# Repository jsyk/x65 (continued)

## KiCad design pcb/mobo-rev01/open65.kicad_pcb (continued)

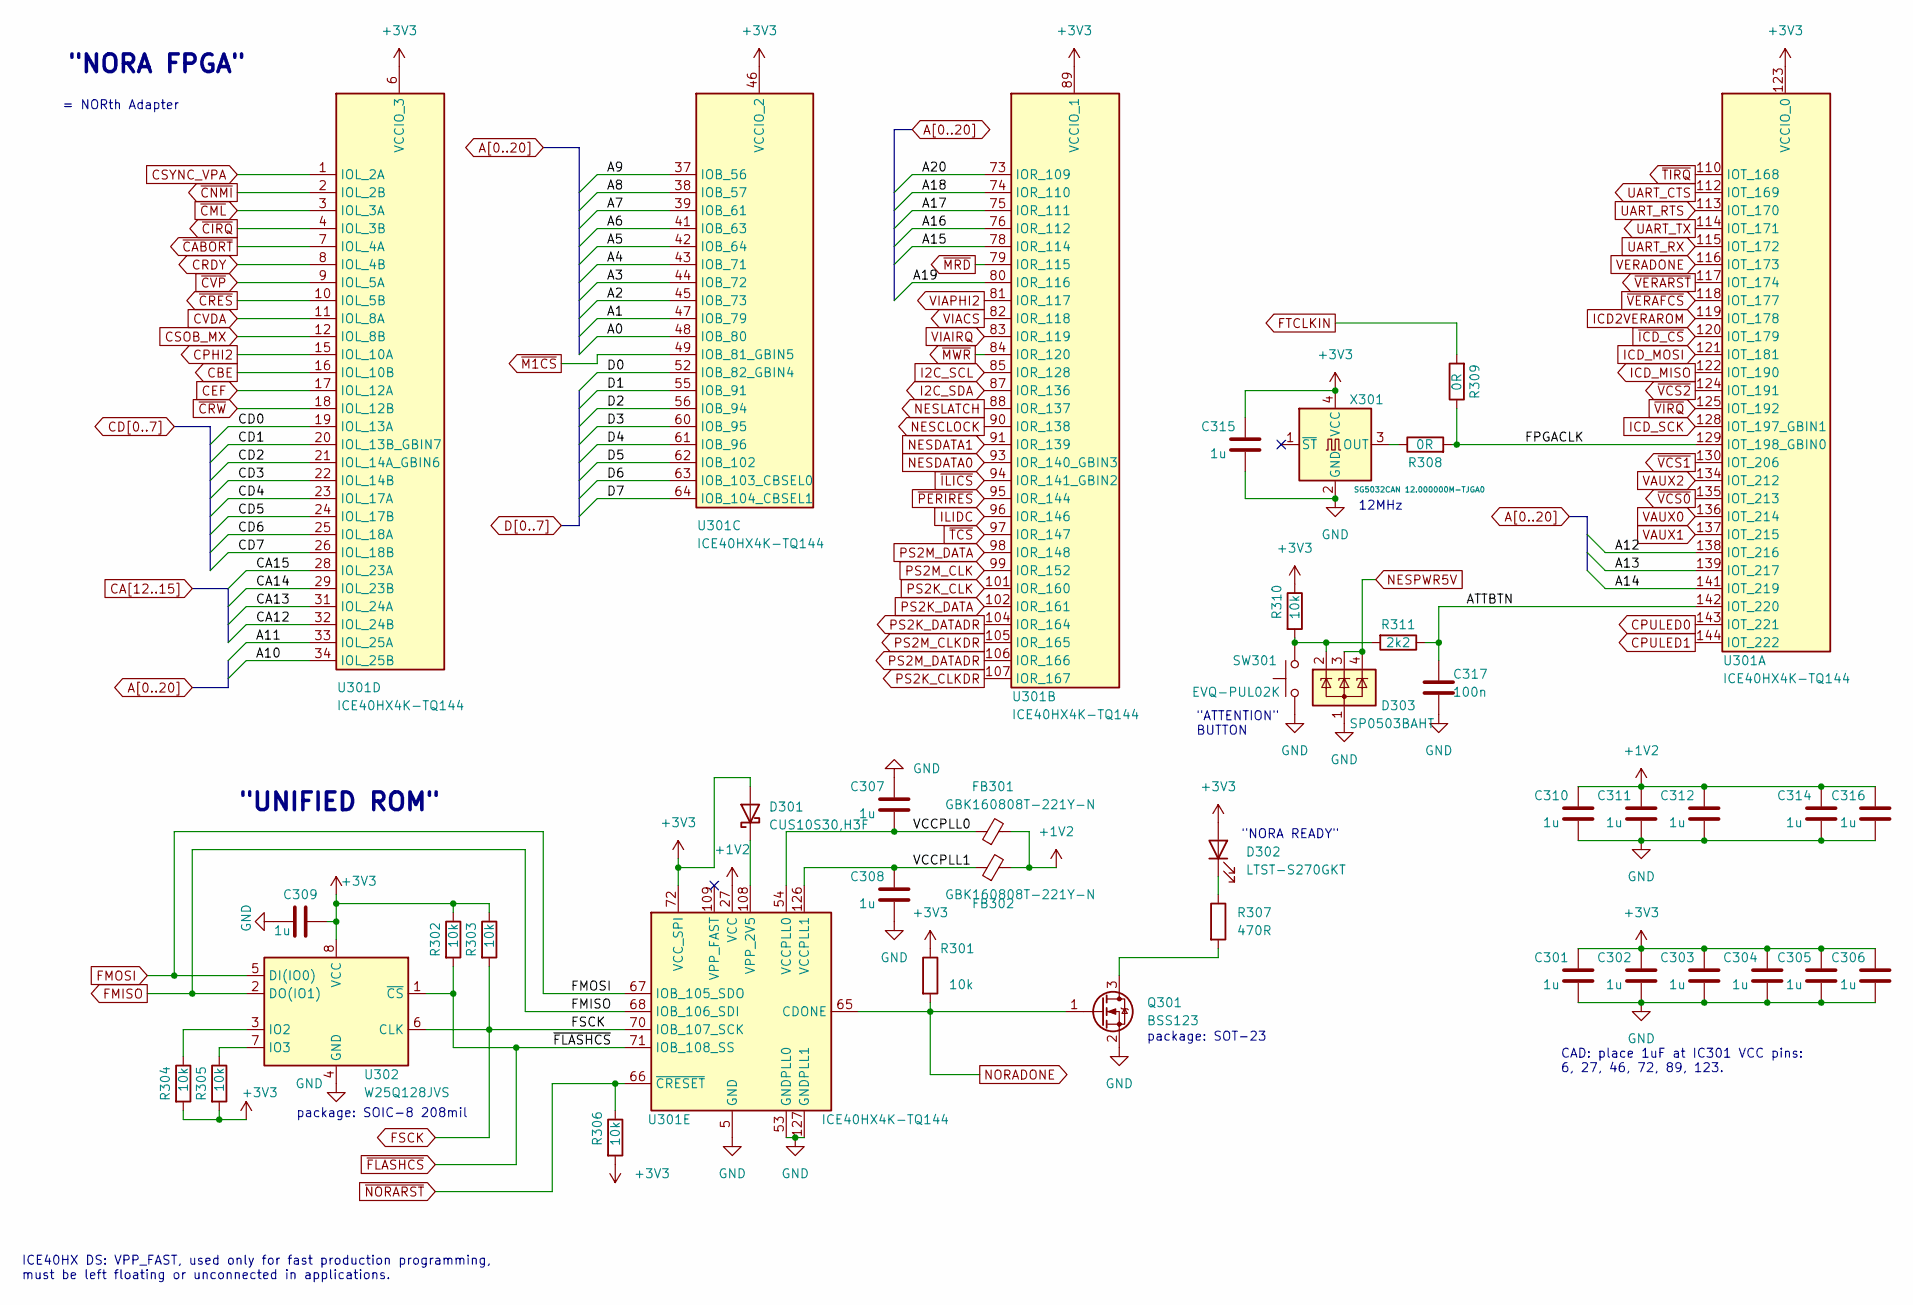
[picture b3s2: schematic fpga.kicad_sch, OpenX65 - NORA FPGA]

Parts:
C301, C302, C303, C304, C305, C306, C307, C308, C309, C310, C311, C312, C314, C315, C316: 1u; C_0603_1608Metric_Pad1.08x0.95mm_HandSolder
C317: 100n; C_0603_1608Metric_Pad1.08x0.95mm_HandSolder
D301: CUS10S30,H3F; D_SOD-323_HandSoldering
D302: LTST-S270GKT; LED_0603_1608Metric_Pad1.05x0.95mm_HandSolder
D303: SP0503BAHT; SOT-143
FB301, FB302: GBK160808T-221Y-N; R_0603_1608Metric_Pad0.98x0.95mm_HandSolder
Q301: BSS123; SOT-23
R301, R302, R303, R304, R305, R306, R310: 10k; R_0603_1608Metric_Pad0.98x0.95mm_HandSolder
R307: 470R; R_0603_1608Metric_Pad0.98x0.95mm_HandSolder
R308, R309: 0R; R_0603_1608Metric_Pad0.98x0.95mm_HandSolder
R311: 2k2; R_0603_1608Metric_Pad0.98x0.95mm_HandSolder
SW301: EVQ-PUL02K; Panasonic_EVQPUL_EVQPUC
U301: ICE40HX4K-TQ144; TQFP-144_20x20mm_P0.5mm
U302: W25Q128JVS; SOIC-8_5.23x5.23mm_P1.27mm
X301: SG5032CAN 12.000000M-TJGA0; Oscillator_SMD_SeikoEpson_SG8002LB-4Pin_5.0x3.2mm_HandSolde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

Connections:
+1V2: C310.1, C311.1, C312.1, C314.1, C316.1, FB301.2, FB302.2, U301.27 (VCC), U301.40 (VCC), U301.92 (VCC), U301.111 (VCC); also elsewhere on the board
+3V3: C301.1, C302.1, C303.1, C304.1, C305.1, C306.1, C309.1, C315.1, D301.2 (A), D302.2 (A), R301.1, R302.1, R303.1, R304.2, R305.2, R306.2, R310.1, U301.6 (VCCIO_3), U301.30 (VCCIO_3), U301.46 (VCCIO_2), U301.57 (VCCIO_2), U301.72 (VCC_SPI), U301.89 (VCCIO_1), U301.100 (VCCIO_1), U301.123 (VCCIO_0), U301.131 (VCCIO_0), U302.8 (VCC), X301.4 (VCC); also elsewhere on the board
/FPGA/ATTBTN: C317.1, R311.1, U301.142 (IOT_220)
/FPGA/FPGACLK: R308.2, R309.1, U301.129 (IOT_198_GBIN0)
/FPGA/VCCPLL0: C307.2, FB301.1, U301.54 (VCCPLL0)
/FPGA/VCCPLL1: C308.1, FB302.1, U301.126 (VCCPLL1)
A0: U301.48 (IOB_80); also elsewhere on the board
A1: U301.47 (IOB_79); also elsewhere on the board
A2: U301.45 (IOB_73); also elsewhere on the board
A3: U301.44 (IOB_72); also elsewhere on the board
A4: U301.43 (IOB_71); also elsewhere on the board
A5: U301.42 (IOB_64); also elsewhere on the board
A6: U301.41 (IOB_63); also elsewhere on the board
A7: U301.39 (IOB_61); also elsewhere on the board
A8: U301.38 (IOB_57); also elsewhere on the board
A9: U301.37 (IOB_56); also elsewhere on the board
A10: U301.34 (IOL_25B); also elsewhere on the board
A11: U301.33 (IOL_25A); also elsewhere on the board
A12: U301.138 (IOT_216); also elsewhere on the board
A13: U301.139 (IOT_217); also elsewhere on the board
A14: U301.141 (IOT_219); also elsewhere on the board
A15: U301.78 (IOR_114); also elsewhere on the board
A16: U301.76 (IOR_112); also elsewhere on the board
A17: U301.75 (IOR_111); also elsewhere on the board
A18: U301.74 (IOR_110); also elsewhere on the board
A19: U301.80 (IOR_116); also elsewhere on the board
A20: U301.73 (IOR_109); also elsewhere on the board
CA12: U301.32 (IOL_24B); also elsewhere on the board
CA13: U301.31 (IOL_24A); also elsewhere on the board
CA14: U301.29 (IOL_23B); also elsewhere on the board
CA15: U301.28 (IOL_23A); also elsewhere on the board
CBE: U301.16 (IOL_10B); also elsewhere on the board
CD0: U301.19 (IOL_13A); also elsewhere on the board
CD1: U301.20 (IOL_13B_GBIN7); also elsewhere on the board
CD2: U301.21 (IOL_14A_GBIN6); also elsewhere on the board
CD3: U301.22 (IOL_14B); also elsewhere on the board
CD4: U301.23 (IOL_17A); also elsewhere on the board
CD5: U301.24 (IOL_17B); also elsewhere on the board
CD6: U301.25 (IOL_18A); also elsewhere on the board
CD7: U301.26 (IOL_18B); also elsewhere on the board
CEF: U301.17 (IOL_12A); also elsewhere on the board
CPHI2: U301.15 (IOL_10A); also elsewhere on the board
CPULED0: U301.143 (IOT_221); also elsewhere on the board
CPULED1: U301.144 (IOT_222); also elsewhere on the board
CRDY: U301.8 (IOL_4B); also elsewhere on the board
CSOB_MX: U301.12 (IOL_8B); also elsewhere on the board
CSYNC_VPA: U301.1 (IOL_2A); also elsewhere on the board
CVDA: U301.11 (IOL_8A); also elsewhere on the board
D0: U301.52 (IOB_82_GBIN4); also elsewhere on the board
D1: U301.55 (IOB_91); also elsewhere on the board
D2: U301.56 (IOB_94); also elsewhere on the board
D3: U301.60 (IOB_95); also elsewhere on the board
D4: U301.61 (IOB_96); also elsewhere on the board
D5: U301.62 (IOB_102); also elsewhere on the board
D6: U301.63 (IOB_103_CBSEL0); also elsewhere on the board
D7: U301.64 (IOB_104_CBSEL1); also elsewhere on the board
FMISO: U301.68 (IOB_106_SDI), U302.2 (DO(IO1)); also elsewhere on the board
FMOSI: U301.67 (IOB_105_SDO), U302.5 (DI(IO0)); also elsewhere on the board
FSCK: R303.2, U301.70 (IOB_107_SCK), U302.6 (CLK); also elsewhere on the board
FTCLKIN: R309.2; also elsewhere on the board
GND: C301.2, C302.2, C303.2, C304.2, C305.2, C306.2, C307.1, C308.2, C309.2, C310.2, C311.2, C312.2, C314.2, C315.2, C316.2, C317.2, D303.1 (A), Q301.2 (S), SW301.1, U301.5 (GND), U301.13 (GND), U301.14 (GND), U301.53 (GNDPLL0), U301.59 (GND), U301.69 (GND), U301.86 (GND), U301.103 (GND), U301.127 (GNDPLL1), U301.132 (GND), U301.140 (GND), U302.4 (GND), X301.2 (GND); also elsewhere on the board
I2C_SCL: U301.85 (IOR_128); also elsewhere on the board
I2C_SDA: U301.87 (IOR_136); also elsewhere on the board
ICD2VERAROM: U301.119 (IOT_178); also elsewhere on the board
ICD_MISO: U301.122 (IOT_190); also elsewhere on the board
ICD_MOSI: U301.121 (IOT_181); also elsewhere on the board
ICD_SCK: U301.128 (IOT_197_GBIN1); also elsewhere on the board
ILIDC: U301.96 (IOR_146); also elsewhere on the board
NESCLOCK: U301.90 (IOR_138); also elsewhere on the board
NESDATA0: U301.93 (IOR_140_GBIN3); also elsewhere on the board
NESDATA1: U301.91 (IOR_139); also elsewhere on the board
NESLATCH: U301.88 (IOR_137); also elsewhere on the board
NESPWR5V: D303.3 (K), D303.4 (K); also elsewhere on the board
NORADONE: Q301.1 (G), R301.2, U301.65 (CDONE); also elsewhere on the board
unnamed: D301.1 (K), U301.108 (VPP_2V5)
unnamed: D302.1 (K), R307.1
unnamed: D303.2 (K), R310.2, R311.2, SW301.2
unnamed: Q301.3 (D), R307.2
unnamed: R304.1, U302.3 (IO2)
unnamed: R305.1, U302.7 (IO3)
unnamed: R308.1, X301.3 (OUT)
PS2K_CLK: U301.101 (IOR_160); also elsewhere on the board
PS2K_CLKDR: U301.107 (IOR_167); also elsewhere on the board
PS2K_DATA: U301.102 (IOR_161); also elsewhere on the board
PS2K_DATADR: U301.104 (IOR_164); also elsewhere on the board
PS2M_CLK: U301.99 (IOR_152); also elsewhere on the board
PS2M_CLKDR: U301.105 (IOR_165); also elsewhere on the board
PS2M_DATA: U301.98 (IOR_148); also elsewhere on the board
PS2M_DATADR: U301.106 (IOR_166); also elsewhere on the board
UART_CTS: U301.112 (IOT_169); also elsewhere on the board
UART_RTS: U301.113 (IOT_170); also elsewhere on the board
UART_RX: U301.115 (IOT_172); also elsewhere on the board
UART_TX: U301.114 (IOT_171); also elsewhere on the board
VAUX0: U301.136 (IOT_214); also elsewhere on the board
VAUX1: U301.137 (IOT_215); also elsewhere on the board
VAUX2: U301.134 (IOT_212); also elsewhere on the board
VERADONE: U301.116 (IOT_173); also elsewhere on the board
VIACS: U301.82 (IOR_118); also elsewhere on the board
VIAIRQ: U301.83 (IOR_119); also elsewhere on the board
VIAPHI2: U301.81 (IOR_117); also elsewhere on the board
~CABORT: U301.7 (IOL_4A); also elsewhere on the board
~CIRQ: U301.4 (IOL_3B); also elsewhere on the board
~CML: U301.3 (IOL_3A); also elsewhere on the board
~CNMI: U301.2 (IOL_2B); also elsewhere on the board
~CRES: U301.10 (IOL_5B); also elsewhere on the board
~CRW: U301.18 (IOL_12B); also elsewhere on the board
~CVP: U301.9 (IOL_5A); also elsewhere on the board
~FLASHCS: R302.2, U301.71 (IOB_108_SS), U302.1 (~CS); also elsewhere on the board
~ICD_CS: U301.120 (IOT_179); also elsewhere on the board
~ILICS: U301.94 (IOR_141_GBIN2); also elsewhere on the board
~M1CS: U301.49 (IOB_81_GBIN5); also elsewhere on the board
~MRD: U301.79 (IOR_115); also elsewhere on the board
~MWR: U301.84 (IOR_120); also elsewhere on the board
~NORARST: R306.1, U301.66 (~CRESET); also elsewhere on the board
~PERIRES: U301.95 (IOR_144); also elsewhere on the board
~TCS: U301.97 (IOR_147); also elsewhere on the board
~TIRQ: U301.110 (IOT_168); also elsewhere on the board
~VCS0: U301.135 (IOT_213); also elsewhere on the board
~VCS1: U301.130 (IOT_206); also elsewhere on the board
~VCS2: U301.124 (IOT_191); also elsewhere on the board
~VERAFCS: U301.118 (IOT_177); also elsewhere on the board
~VERARST: U301.117 (IOT_174); also elsewhere on the board
~VIRQ: U301.125 (IOT_192); also elsewhere on the board

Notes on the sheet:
package: SOIC-8 208mil
12MHz
= NORth Adapter
ICE40HX DS: VPP_FAST, used only for fast production programming, must be left floating or unconnected in applications.
"NORA READY"
"NORA FPGA"
"UNIFIED ROM"
package: SOT-23
"ATTENTION" BUTTON
CAD: place 1uF at IC301 VCC pins: 6, 27, 46, 72, 89, 123.

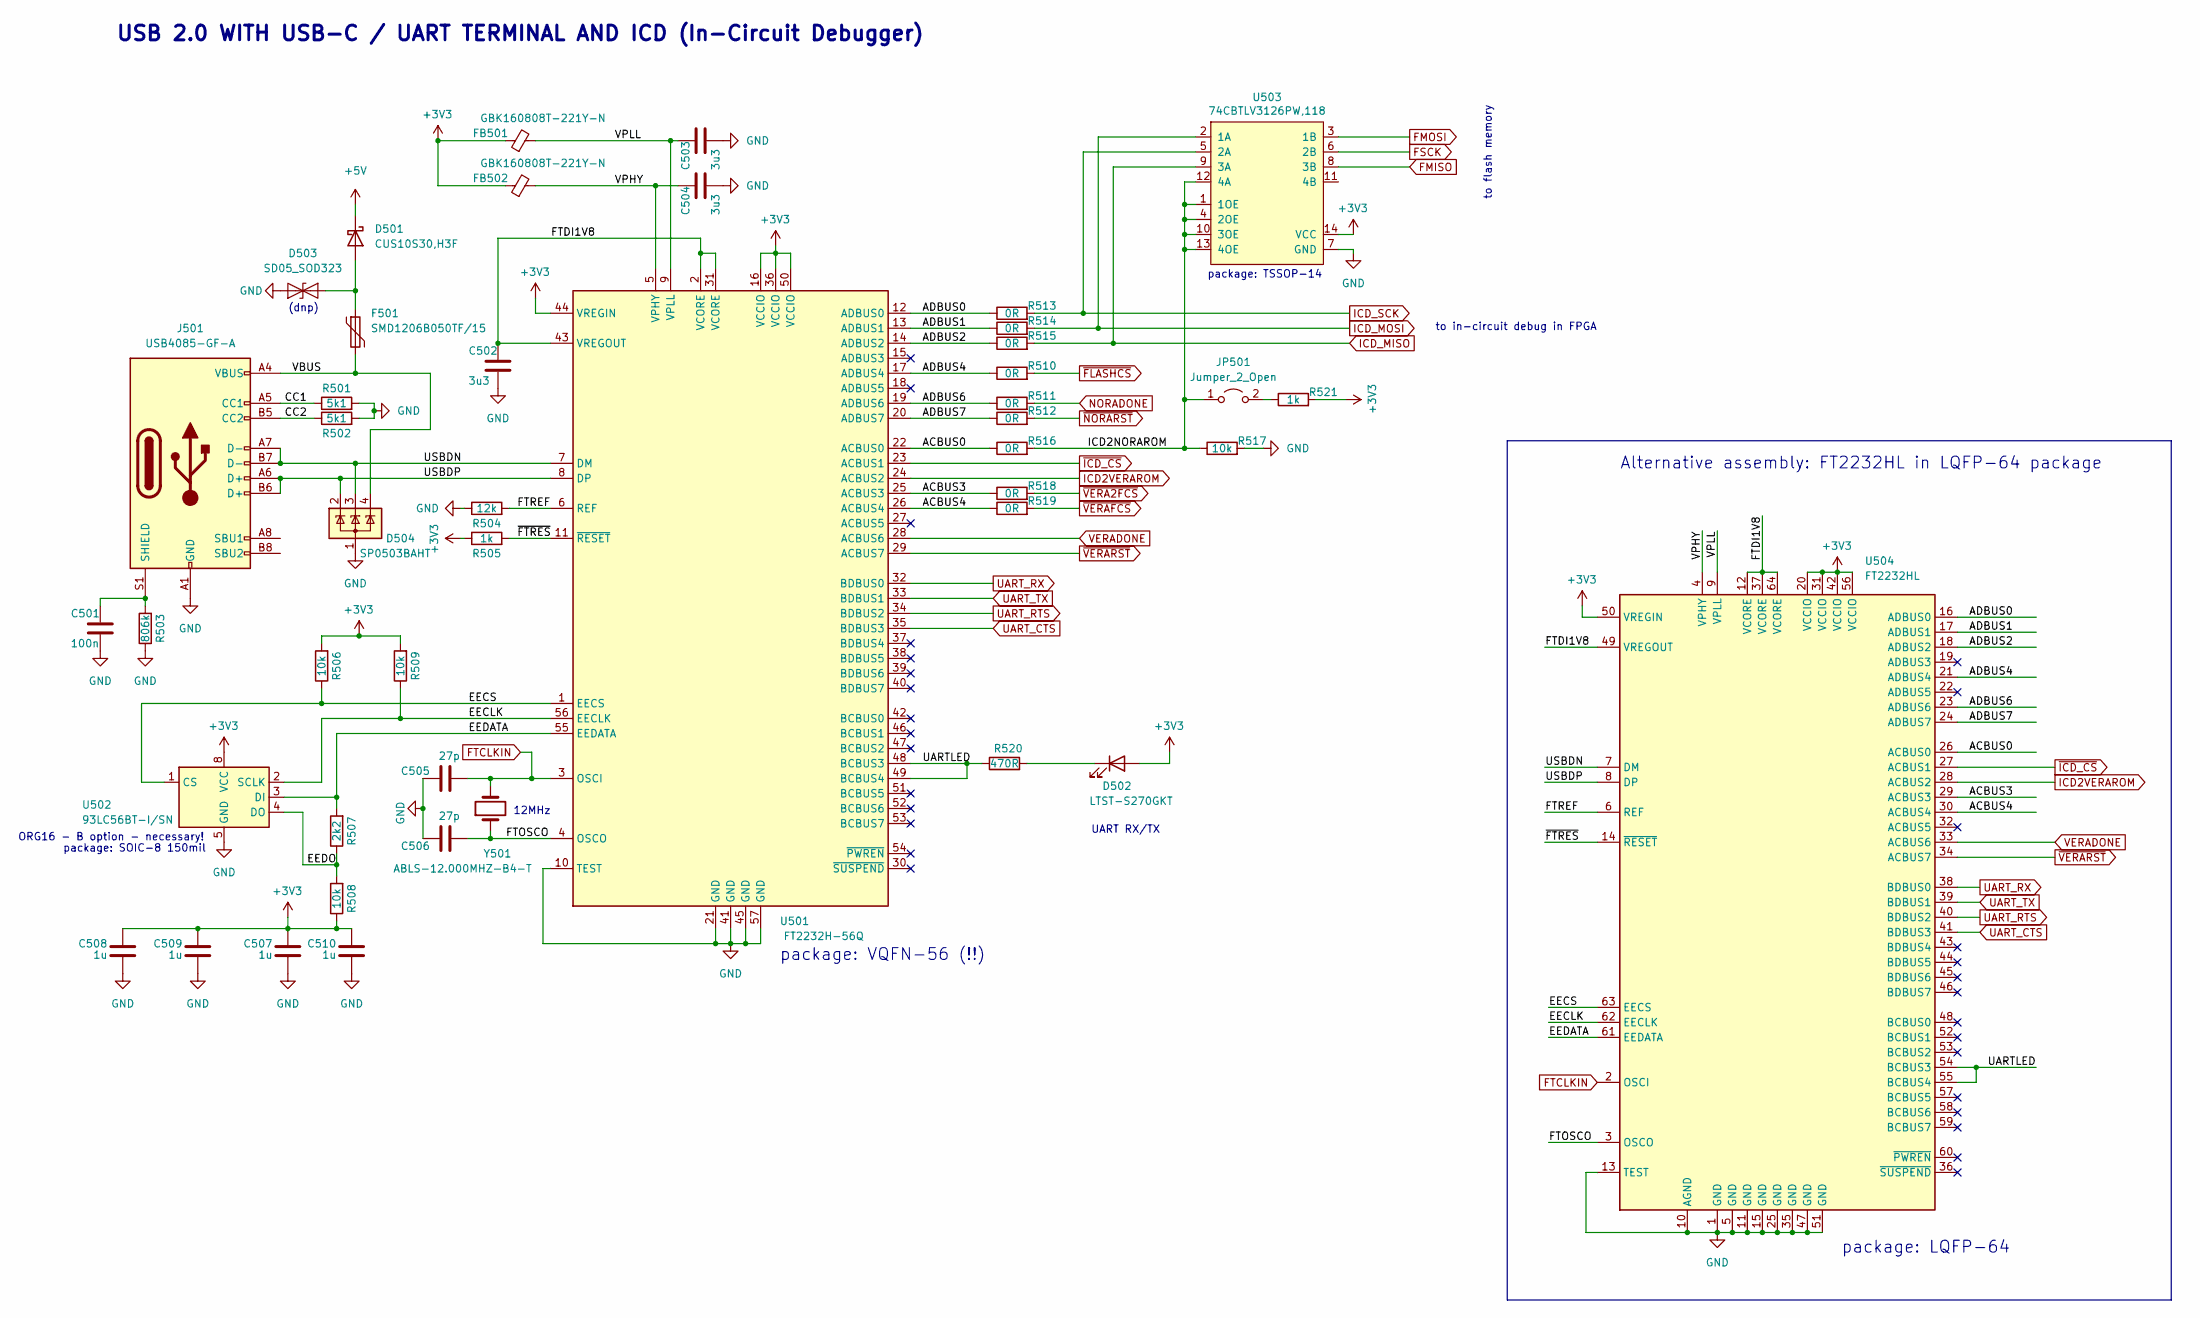
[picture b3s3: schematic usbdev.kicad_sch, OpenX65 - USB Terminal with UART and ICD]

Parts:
C501: 100n; C_0603_1608Metric_Pad1.08x0.95mm_HandSolder
C502, C503, C504: 3u3; C_0603_1608Metric_Pad1.08x0.95mm_HandSolder
C505, C506: 27p; C_0603_1608Metric_Pad1.08x0.95mm_HandSolder
C507, C508, C509, C510: 1u; C_0603_1608Metric_Pad1.08x0.95mm_HandSolder
D501: CUS10S30,H3F; D_SOD-323_HandSoldering
D502: LTST-S270GKT; LED_0603_1608Metric_Pad1.05x0.95mm_HandSolder
D503: SD05_SOD323; D_SOD-323
D504: SP0503BAHT; SOT-143
F501: SMD1206B050TF/15; Fuse_1206_3216Metric_Pad1.42x1.75mm_HandSolder
FB501, FB502: GBK160808T-221Y-N; R_0603_1608Metric_Pad0.98x0.95mm_HandSolder
J501: USB4085-GF-A; USB_C_Receptacle_GCT_USB4085
JP501: Jumper_2_Open; PinHeader_1x02_P2.54mm_Vertical
R501, R502: 5k1; R_0603_1608Metric_Pad0.98x0.95mm_HandSolder
R503: 806k; R_0603_1608Metric_Pad0.98x0.95mm_HandSolder
R504: 12k; R_0603_1608Metric_Pad0.98x0.95mm_HandSolder
R505, R521: 1k; R_0603_1608Metric_Pad0.98x0.95mm_HandSolder
R506, R508, R509, R517: 10k; R_0603_1608Metric_Pad0.98x0.95mm_HandSolder
R507: 2k2; R_0603_1608Metric_Pad0.98x0.95mm_HandSolder
R510, R511, R512, R513, R514, R515, R516, R518, R519: 0R; R_0603_1608Metric_Pad0.98x0.95mm_HandSolder
R520: 470R; R_0603_1608Metric_Pad0.98x0.95mm_HandSolder
U501: FT2232H-56Q; QFN-56-1EP_8x8mm_P0.5mm_EP4.5x5.2mm
U502: 93LC56BT-I/SN; SOIC-8_3.9x4.9mm_P1.27mm
U503: 74CBTLV3126PW,118; TSSOP-14_4.4x5mm_P0.65mm
U504: FT2232HL; LQFP-64_10x10mm_P0.5mm
Y501: ABLS-12.000MHZ-B4-T; Crystal_SMD_Abracon_ABM3-2Pin_5.0x3.2mm_HandSoldering

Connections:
+3V3: C507.1, C508.1, C509.1, C510.1, D502.2 (A), FB501.1, FB502.1, R505.1, R506.2, R508.1, R509.2, R521.2, U501.16 (VCCIO), U501.36 (VCCIO), U501.44 (VREGIN), U501.50 (VCCIO), U502.8 (VCC), U503.14 (VCC), U504.20 (VCCIO), U504.31 (VCCIO), U504.42 (VCCIO), U504.50 (VREGIN), U504.56 (VCCIO); also elsewhere on the board
+5V: D501.1 (K); also elsewhere on the board
/USB-Terminal/ACBUS0: R516.1, U501.22 (ACBUS0), U504.26 (ACBUS0)
/USB-Terminal/ACBUS3: R518.1, U501.25 (ACBUS3), U504.29 (ACBUS3)
/USB-Terminal/ACBUS4: R519.1, U501.26 (ACBUS4), U504.30 (ACBUS4)
/USB-Terminal/ADBUS0: R513.1, U501.12 (ADBUS0), U504.16 (ADBUS0)
/USB-Terminal/ADBUS1: R514.1, U501.13 (ADBUS1), U504.17 (ADBUS1)
/USB-Terminal/ADBUS2: R515.1, U501.14 (ADBUS2), U504.18 (ADBUS2)
/USB-Terminal/ADBUS4: R510.1, U501.17 (ADBUS4), U504.21 (ADBUS4)
/USB-Terminal/ADBUS6: R511.1, U501.19 (ADBUS6), U504.23 (ADBUS6)
/USB-Terminal/ADBUS7: R512.1, U501.20 (ADBUS7), U504.24 (ADBUS7)
/USB-Terminal/CC1: J501.A5 (CC1), R501.1
/USB-Terminal/CC2: J501.B5 (CC2), R502.1
/USB-Terminal/EECLK: R509.1, U501.56 (EECLK), U502.2 (SCLK), U504.62 (EECLK)
/USB-Terminal/EECS: R506.1, U501.1 (EECS), U502.1 (CS), U504.63 (EECS)
/USB-Terminal/EEDATA: R507.2, U501.55 (EEDATA), U502.3 (DI), U504.61 (EEDATA)
/USB-Terminal/EEDO: R507.1, R508.2, U502.4 (DO)
/USB-Terminal/FTDI1V8: C502.1, U501.2 (VCORE), U501.31 (VCORE), U501.43 (VREGOUT), U504.12 (VCORE), U504.37 (VCORE), U504.49 (VREGOUT), U504.64 (VCORE)
/USB-Terminal/FTOSCO: C506.2, U501.4 (OSCO), U504.3 (OSCO), Y501.1
/USB-Terminal/FTREF: R504.2, U501.6 (REF), U504.6 (REF)
/USB-Terminal/ICD2NORAROM: JP501.1 (A), R516.2, R517.1, U503.1 (1OE), U503.4 (2OE), U503.10 (3OE), U503.12 (4A), U503.13 (4OE)
/USB-Terminal/UARTLED: R520.1, U501.48 (BCBUS3), U501.49 (BCBUS4), U504.54 (BCBUS3), U504.55 (BCBUS4)
/USB-Terminal/USBDN: D504.3 (K), J501.A7 (D-), J501.B7 (D-), U501.7 (DM), U504.7 (DM)
/USB-Terminal/USBDP: D504.2 (K), J501.A6 (D+), J501.B6 (D+), U501.8 (DP), U504.8 (DP)
/USB-Terminal/VBUS: D504.4 (K), F501.2, J501.A4 (VBUS), J501.A9 (VBUS), J501.B4 (VBUS), J501.B9 (VBUS)
/USB-Terminal/VPHY: C504.1, FB502.2, U501.5 (VPHY), U504.4 (VPHY)
/USB-Terminal/VPLL: C503.1, FB501.2, U501.9 (VPLL), U504.9 (VPLL)
/USB-Terminal/~FTRES: R505.2, U501.11 (~RESET), U504.14 (~RESET)
FMISO: U503.8 (3B); also elsewhere on the board
FMOSI: U503.3 (1B); also elsewhere on the board
FSCK: U503.6 (2B); also elsewhere on the board
FTCLKIN: C505.2, U501.3 (OSCI), U504.2 (OSCI), Y501.2; also elsewhere on the board
GND: C501.2, C502.2, C503.2, C504.2, C505.1, C506.1, C507.2, C508.2, C509.2, C510.2, D503.1 (A1), D504.1 (A), J501.A1 (GND), J501.A12 (GND), J501.B1 (GND), J501.B12 (GND), R501.2, R502.2, R503.1, R504.1, R517.2, U501.10 (TEST), U501.21 (GND), U501.41 (GND), U501.45 (GND), U501.57 (GND), U502.5 (GND), U503.7 (GND), U504.1 (GND), U504.5 (GND), U504.10 (AGND), U504.11 (GND), U504.13 (TEST), U504.15 (GND), U504.25 (GND), U504.35 (GND), U504.47 (GND), U504.51 (GND); also elsewhere on the board
ICD2VERAROM: U501.24 (ACBUS2), U504.28 (ACBUS2); also elsewhere on the board
ICD_MISO: R515.2, U503.9 (3A); also elsewhere on the board
ICD_MOSI: R514.2, U503.2 (1A); also elsewhere on the board
ICD_SCK: R513.2, U503.5 (2A); also elsewhere on the board
NORADONE: R511.2; also elsewhere on the board
unnamed: C501.1, J501.S1 (SHIELD), R503.2
unnamed: D501.2 (A), D503.2 (A2), F501.1
unnamed: D502.1 (K), R520.2
unnamed: JP501.2 (B), R521.1
UART_CTS: U501.35 (BDBUS3), U504.41 (BDBUS3); also elsewhere on the board
UART_RTS: U501.34 (BDBUS2), U504.40 (BDBUS2); also elsewhere on the board
UART_RX: U501.32 (BDBUS0), U504.38 (BDBUS0); also elsewhere on the board
UART_TX: U501.33 (BDBUS1), U504.39 (BDBUS1); also elsewhere on the board
VERADONE: U501.28 (ACBUS6), U504.33 (ACBUS6); also elsewhere on the board
~FLASHCS: R510.2; also elsewhere on the board
~ICD_CS: U501.23 (ACBUS1), U504.27 (ACBUS1); also elsewhere on the board
~NORARST: R512.2; also elsewhere on the board
~VERA2FCS: R518.2; also elsewhere on the board
~VERAFCS: R519.2; also elsewhere on the board
~VERARST: U501.29 (ACBUS7), U504.34 (ACBUS7); also elsewhere on the board

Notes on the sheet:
12MHz
package: SOIC-8 150mil
to in-circuit debug in FPGA
package: LQFP-64
to flash memory
ORG16 - B option - necessary!
package: TSSOP-14
UART RX/TX
Alternative assembly: FT2232HL in LQFP-64 package
package: VQFN-56 (!!)
(dnp)
USB 2.0 WITH USB-C / UART TERMINAL AND ICD (In-Circuit Debugger)

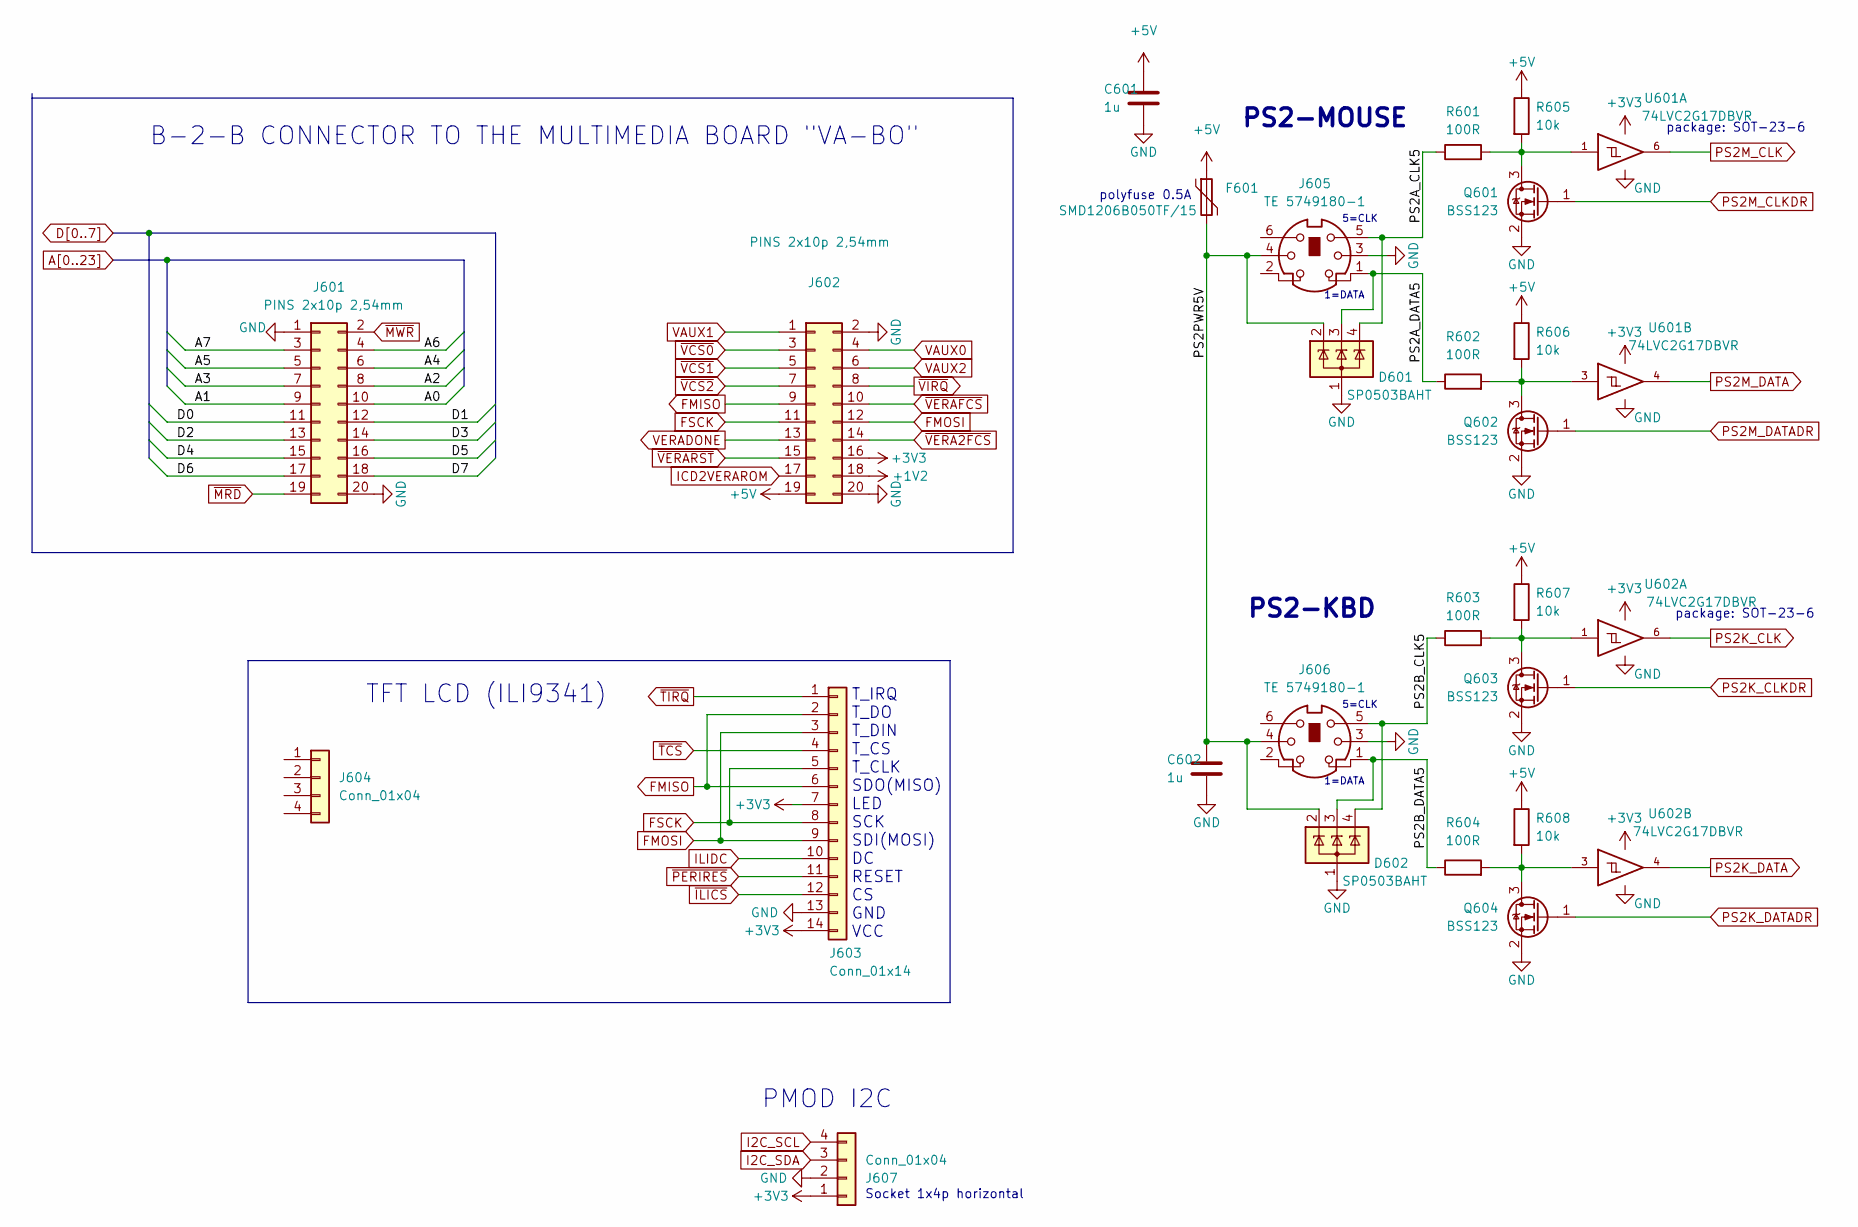
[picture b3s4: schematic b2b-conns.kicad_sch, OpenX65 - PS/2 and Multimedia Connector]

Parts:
C601, C602: 1u; C_0603_1608Metric_Pad1.08x0.95mm_HandSolder
D601, D602: SP0503BAHT; SOT-143
F601: SMD1206B050TF/15; Fuse_1206_3216Metric_Pad1.42x1.75mm_HandSolder
J601, J602: PINS 2x10p 2,54mm; PinHeader_2x10_P2.54mm_Vertical
J603: Conn_01x14; PinSocket_1x14_P2.54mm_Vertical
J604: Conn_01x04; PinSocket_1x04_P2.54mm_Vertical_SMD_Pin1Left
J605, J606: TE 5749180-1; TE_5749180-1
J607: Conn_01x04; PinSocket_1x04_P2.54mm_Horizontal
Q601, Q602, Q603, Q604: BSS123; SOT-23
R601, R602, R603, R604: 100R; R_0603_1608Metric_Pad0.98x0.95mm_HandSolder
R605, R606, R607, R608: 10k; R_0603_1608Metric_Pad0.98x0.95mm_HandSolder
U601, U602: 74LVC2G17DBVR; SOT-23-6_Handsoldering

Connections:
+1V2: J602.18; also elsewhere on the board
+3V3: J602.16, J603.7, J603.14, J607.1, U601.5 (VCC), U602.5 (VCC); also elsewhere on the board
+5V: C601.1, F601.1, J602.19, R605.1, R606.1, R607.1, R608.1; also elsewhere on the board
/VA-Board, PS2/PS2A_CLK5: D601.4 (K), J605.5, R601.1
/VA-Board, PS2/PS2A_DATA5: D601.3 (K), J605.1, R602.1
/VA-Board, PS2/PS2B_CLK5: D602.4 (K), J606.5, R603.1
/VA-Board, PS2/PS2B_DATA5: D602.3 (K), J606.1, R604.1
/VA-Board, PS2/PS2PWR5V: C602.1, D601.2 (K), D602.2 (K), F601.2, J605.4, J606.4
A0: J601.10; also elsewhere on the board
A1: J601.9; also elsewhere on the board
A2: J601.8; also elsewhere on the board
A3: J601.7; also elsewhere on the board
A4: J601.6; also elsewhere on the board
A5: J601.5; also elsewhere on the board
A6: J601.4; also elsewhere on the board
A7: J601.3; also elsewhere on the board
D0: J601.11; also elsewhere on the board
D1: J601.12; also elsewhere on the board
D2: J601.13; also elsewhere on the board
D3: J601.14; also elsewhere on the board
D4: J601.15; also elsewhere on the board
D5: J601.16; also elsewhere on the board
D6: J601.17; also elsewhere on the board
D7: J601.18; also elsewhere on the board
FMISO: J602.9, J603.2, J603.6; also elsewhere on the board
FMOSI: J602.12, J603.3, J603.9; also elsewhere on the board
FSCK: J602.11, J603.5, J603.8; also elsewhere on the board
GND: C601.2, C602.2, D601.1 (A), D602.1 (A), J601.1, J601.20, J602.2, J602.20, J603.13, J605.3, J606.3, J607.2, Q601.2 (S), Q602.2 (S), Q603.2 (S), Q604.2 (S), U601.2 (GND), U602.2 (GND); also elsewhere on the board
I2C_SCL: J607.4; also elsewhere on the board
I2C_SDA: J607.3; also elsewhere on the board
ICD2VERAROM: J602.17; also elsewhere on the board
ILIDC: J603.10; also elsewhere on the board
unnamed: Q601.3 (D), R601.2, R605.2, U601.1
unnamed: Q602.3 (D), R602.2, R606.2, U601.3
unnamed: Q603.3 (D), R603.2, R607.2, U602.1
unnamed: Q604.3 (D), R604.2, R608.2, U602.3
PS2K_CLK: U602.6; also elsewhere on the board
PS2K_CLKDR: Q603.1 (G); also elsewhere on the board
PS2K_DATA: U602.4; also elsewhere on the board
PS2K_DATADR: Q604.1 (G); also elsewhere on the board
PS2M_CLK: U601.6; also elsewhere on the board
PS2M_CLKDR: Q601.1 (G); also elsewhere on the board
PS2M_DATA: U601.4; also elsewhere on the board
PS2M_DATADR: Q602.1 (G); also elsewhere on the board
VAUX0: J602.4; also elsewhere on the board
VAUX1: J602.1; also elsewhere on the board
VAUX2: J602.6; also elsewhere on the board
VERADONE: J602.13; also elsewhere on the board
~ILICS: J603.12; also elsewhere on the board
~MRD: J601.19; also elsewhere on the board
~MWR: J601.2; also elsewhere on the board
~PERIRES: J603.11; also elsewhere on the board
~TCS: J603.4; also elsewhere on the board
~TIRQ: J603.1; also elsewhere on the board
~VCS0: J602.3; also elsewhere on the board
~VCS1: J602.5; also elsewhere on the board
~VCS2: J602.7; also elsewhere on the board
~VERA2FCS: J602.14; also elsewhere on the board
~VERAFCS: J602.10; also elsewhere on the board
~VERARST: J602.15; also elsewhere on the board
~VIRQ: J602.8; also elsewhere on the board

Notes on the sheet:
Socket 1x4p horizontal
B-2-B CONNECTOR TO THE MULTIMEDIA BOARD "VA-BO"
package: SOT-23-6
1=DATA
5=CLK
polyfuse 0.5A
PS2-MOUSE
PS2-KBD
TFT LCD (ILI9341)
PMOD I2C
T_IRQ T_DO T_DIN T_CS T_CLK SDO(MISO) LED SCK SDI(MOSI) DC RESET CS GND VCC
